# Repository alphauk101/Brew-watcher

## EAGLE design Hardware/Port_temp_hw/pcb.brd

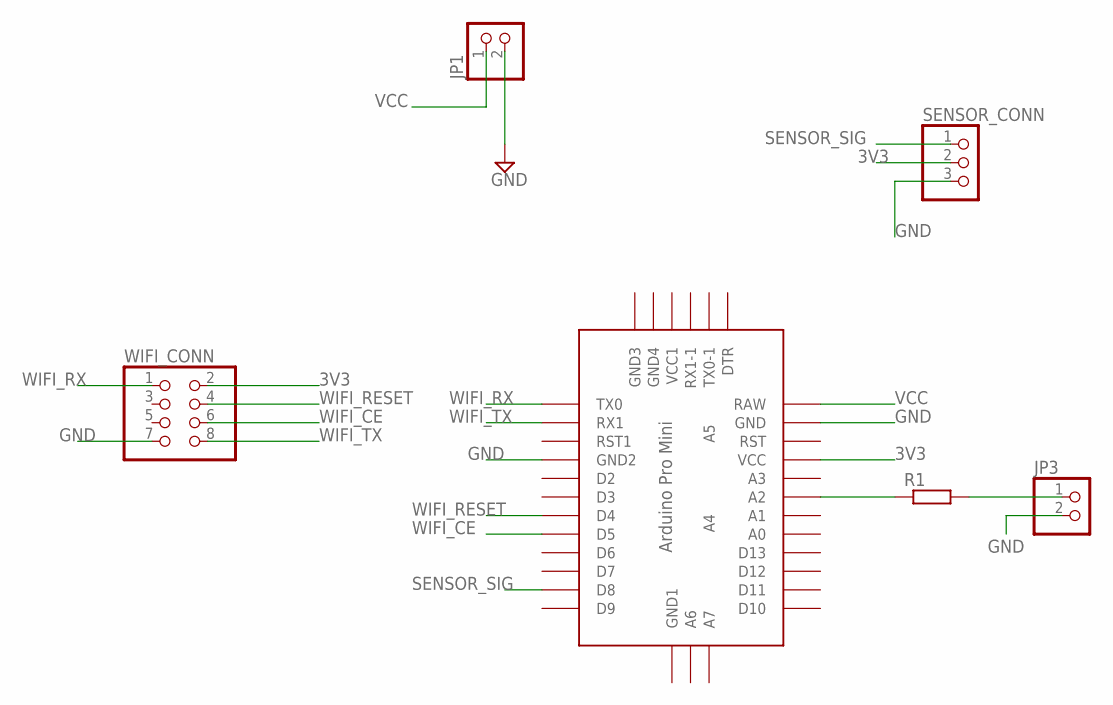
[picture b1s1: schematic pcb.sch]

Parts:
JP1, JP3: PINHD-1X2; 1X02
R1: R0207/10; 0207/10
SENSOR_CONN: PINHD-1X3; 1X03
U$1: ABK-PRO-MINI
WIFI_CONN: PINHD-2X4; 2X04

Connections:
3V3: SENSOR_CONN.2, U$1.VCC, WIFI_CONN.2
GND: JP1.2, JP3.2, SENSOR_CONN.3, U$1.GND, U$1.GND1 (GND2), WIFI_CONN.7
unnamed: JP3.1, R1.2
unnamed: R1.1, U$1.A2
SENSOR_SIG: SENSOR_CONN.1, U$1.D8
VCC: JP1.1, U$1.RAW
WIFI_CE: U$1.D5, WIFI_CONN.6
WIFI_RESET: U$1.D4, WIFI_CONN.4
WIFI_RX: U$1.TX0, WIFI_CONN.1
WIFI_TX: U$1.RX1, WIFI_CONN.8

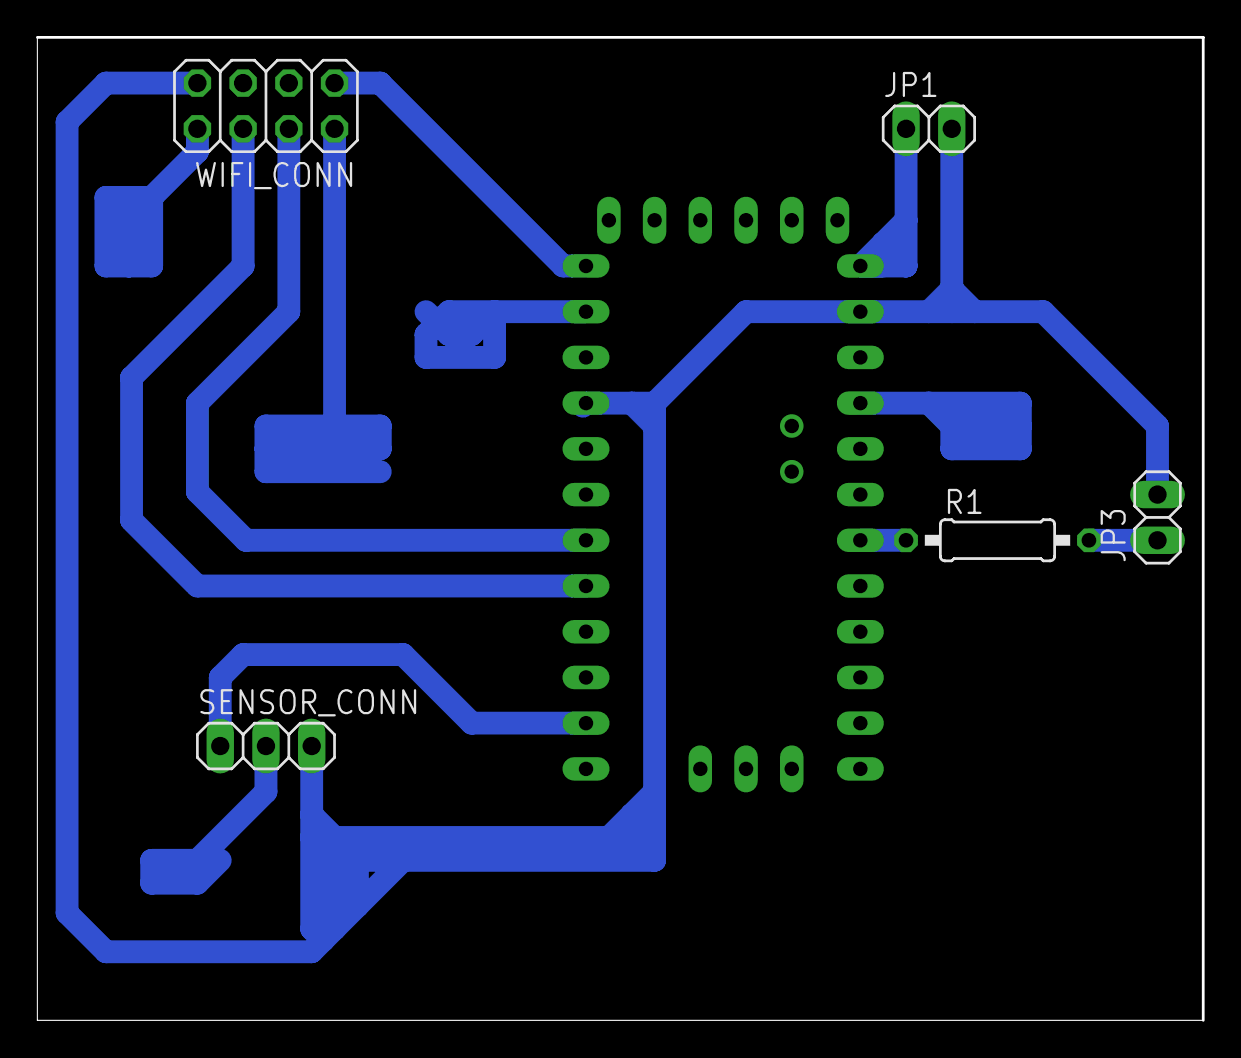
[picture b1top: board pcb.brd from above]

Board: 2 copper layers, 64.8 x 54.6 mm, 6 parts (0 on the bottom side), 10 nets.

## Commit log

2019-08-29 create porta version
2019-08-29 added pcb
2020-05-06 add the water temperature maintainer
